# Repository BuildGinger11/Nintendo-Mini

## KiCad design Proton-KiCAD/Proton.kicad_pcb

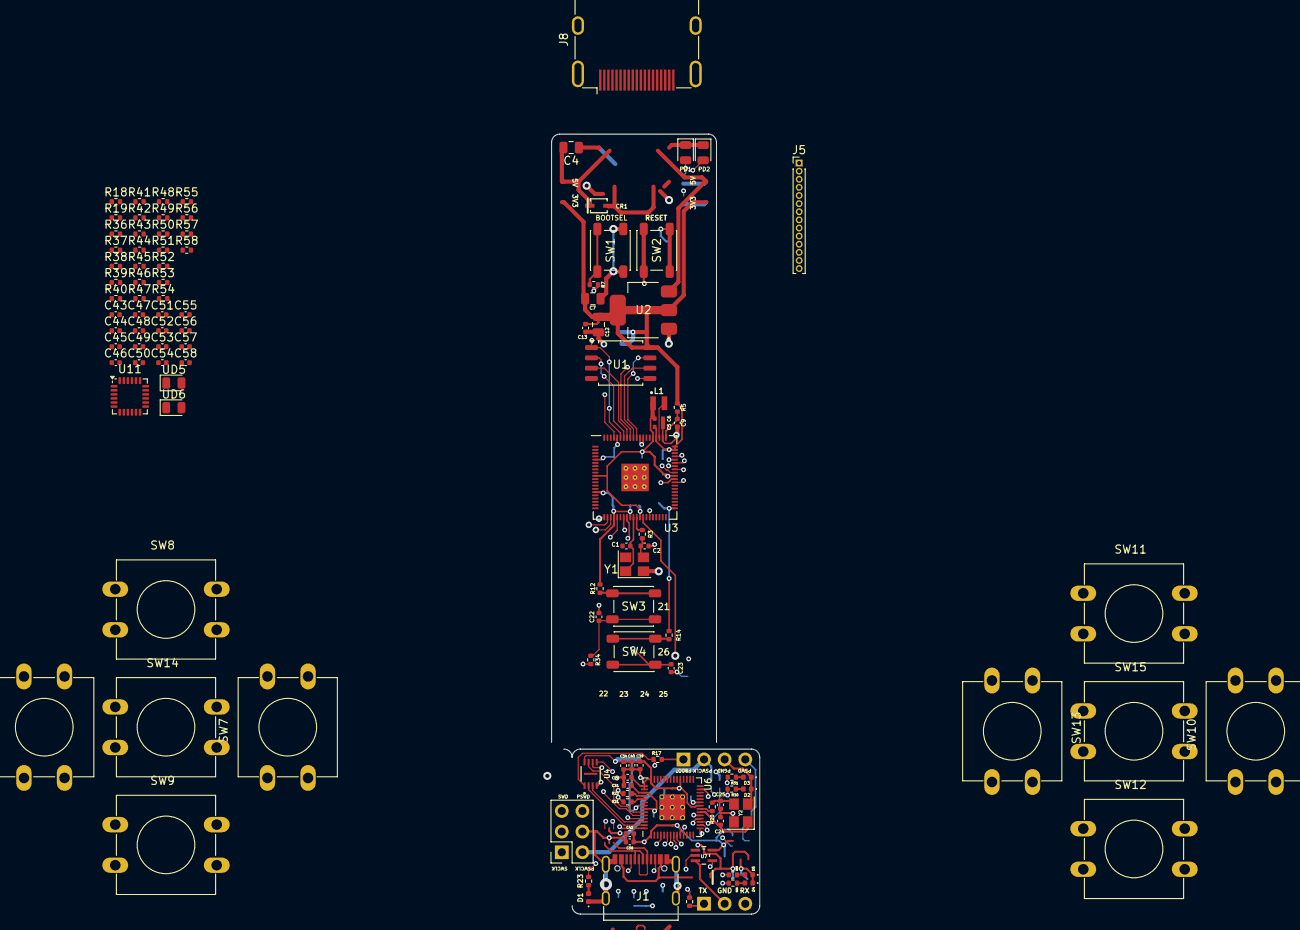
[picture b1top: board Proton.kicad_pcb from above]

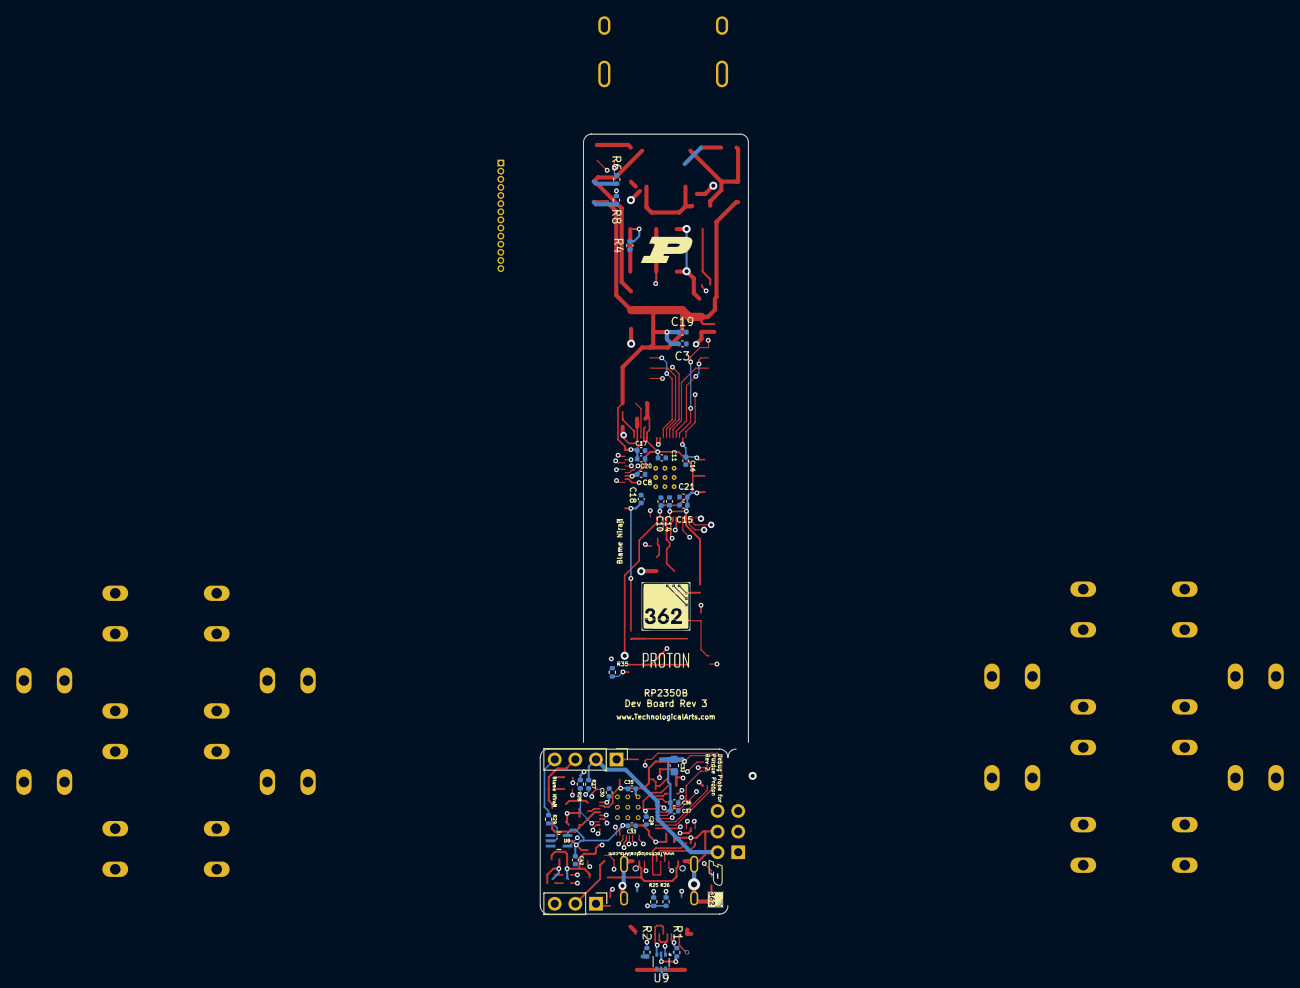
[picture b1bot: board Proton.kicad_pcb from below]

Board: 4 copper layers, 25.6 x 96.1 mm, 150 parts (35 on the bottom side), 91 nets.

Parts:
C1, C2, C24, C25: 15p; C_0402_1005Metric
C3, C8, C11, C13, C14, C15, C16, C17, C18, C19, C20, C21, C22, C23, C28, C29, C30, C33, C35, C36, C37, C38, C39, C40, C41, C42, C43, C44, C45, C46, C47, C48, C49, C50, C57, C58: 100n; C_0402_1005Metric
C4, C7, C12: 10u; C_0805_2012Metric
C5, C6: 4.7u; C_0402_1005Metric_small_pads
C9, C10, C56: 4.7u; C_0402_1005Metric
C31, C34: 1u; C_0402_1005Metric
C32: 10u; C_0603_1608Metric
C51, C53, C54, C55: 0.1u; C_0402_1005Metric
C52: 2.2n; C_0402_1005Metric
CR1: BAT60JFILM; CR_60JFILM_STM
D1: RED; D_0402_1005Metric
D2, D4: GREEN; D_0402_1005Metric
D3, D5: YELLOW; D_0402_1005Metric
J1: USB_C_Receptacle_USB2.0_14P; USB_C_Receptacle_G-Switch_GT-USB-7010ASV
J3: DebugnBoot; PinHeader_1x04_P2.54mm_Vertical
J5: Conn_01x14_Pin; PinHeader_1x14_P1.00mm_Vertical
J6: Conn_02x03_Top_Bottom; PinSocket_2x03_P2.54mm_Vertical
J7: UART-PINS; PinHeader_1x03_P2.54mm_Vertical
J8: HDMI_A; HDMI_A_Molex_208658-1001_Horizontal
L1: 3.3u; L_pol_2016
PD1: RED; LED_0805_2012Metric
PD2: GREEN; LED_0805_2012Metric
R1, R2, R6: 5.1k; R_0402_1005Metric
R3, R4, R7, R8, R12, R14, R17, R18, R19, R20, R36, R38, R40, R42, R44, R45, R46, R47, R55, R57: 1k; R_0402_1005Metric
R5: 33; R_0402_1005Metric
R21, R22: 27; R_0402_1005Metric
R23, R31, R33: 470; R_0402_1005Metric
R24, R25, R26, R27, R28, R29: 100; R_0402_1005Metric
R30, R32: 2k; R_0402_1005Metric
R34, R35, R37, R39, R41, R43, R48, R49, R50, R51, R56, R58: 10k; R_0402_1005Metric
R52: 30k; R_0402_1005Metric
R53, R54: 1.13k; R_0402_1005Metric
SW1: BOOTSEL; SW_SPST_PTS647_Sx38
SW2: RESET; SW_SPST_PTS647_Sx38
SW3: LEFT; SW_SPST_PTS647_Sx38
SW4: RIGHT; SW_SPST_PTS647_Sx38
SW6: LEFT_LEFT; SW_PUSH-12mm
SW7: LEFT_RIGHT; SW_PUSH-12mm
SW8: LEFT_UP; SW_PUSH-12mm
SW9: LEFT_DOWN; SW_PUSH-12mm
SW10: RIGHT_RIGHT; SW_PUSH-12mm
SW11: RIGHT_UP; SW_PUSH-12mm
SW12: RIGHT_DOWN; SW_PUSH-12mm
SW13: RIGHT_LEFT; SW_PUSH-12mm
SW14: LEFT_SEL; SW_PUSH-12mm
SW15: RIGHT_SEL; SW_PUSH-12mm
U1: W25Q128JVS; SOIC-8_5.23x5.23mm_P1.27mm
U2: NCP1117-3.3_SOT223; SOT-223-3_TabPin2
U3: RP2350_80QFN; RP2350-QFN-80-1EP_10x10_P0.4mm_EP3.4x3.4mm_ThermalVias
U4: W25Q16JVUXIQ TR; USON-8_UX_2x3x0p6_WIN
U6: RP2040; RP2040-QFN-56
U7, U8: SN74AUP1T17DCKR; DCK5
U9: USBLC6-2P6; SOT-666
U11: MPU-6050; InvenSense_QFN-24_4x4mm_P0.5mm
UD5, UD6: BLUE; LED_0805_2012Metric
Y1, Y2: ABM8-272-T3; Crystal_SMD_3225-4Pin_3.2x2.5mm

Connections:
+1V1: C6.1, C8.1, C10.1, C11.1, L1.1, U3.10 (DVDD), U3.32 (DVDD), U3.51 (DVDD), U3.65 (VREG_FB)
+3V3: C3.1, C5.1, C7.1, C12.1, C13.1, C14.1, C15.1, C16.1, C17.1, C18.1, C19.1, C20.1, C21.1, C29.1, C32.1, C33.1, C34.1, C35.1, C36.1, C37.1, C38.1, C39.1, C40.1, C41.1, C42.1, C53.1, C56.1, J5.1, R5.1, R8.1, R12.1, R14.1, R18.1, R19.1, R36.1, R38.1, R40.1, R42.1, R44.1, R45.1, R46.1, R47.1, R52.1, R55.1, R57.1, U1.8 (VCC), U2.2 (VO), U3.5 (IOVDD), U3.15 (IOVDD), U3.24 (IOVDD), U3.29 (IOVDD), U3.41 (IOVDD), U3.50 (IOVDD), U3.59 (ADC_AVDD), U3.60 (IOVDD), U3.64 (VREG_VIN), U3.68 (USB_OTP_VDD), U3.69 (QSPI_IOVDD), U3.76 (IOVDD), U4.8 (VCC), U6.1 (IOVDD), U6.10 (IOVDD), U6.22 (IOVDD), U6.33 (IOVDD), U6.42 (IOVDD), U6.43 (ADC_AVDD), U6.44 (VREG_IN), U6.48 (USB_VDD), U6.49 (IOVDD), U7.5 (VCC), U8.5 (VCC), U11.13 (VDD)
+P1V1: C28.1, C30.1, C31.1, U6.23 (DVDD), U6.45 (VREG_VOUT), U6.50 (DVDD)
/DebugProbe/GPIO2: R23.1, U6.4 (GPIO2)
/DebugProbe/GPIO4: R24.1, U6.6 (GPIO4)
/DebugProbe/GPIO5: U6.7 (GPIO5), U7.4 (Y)
/DebugProbe/GPIO6: R25.1, U6.8 (GPIO6)
/DebugProbe/GPIO7: R30.1, U6.9 (GPIO7)
/DebugProbe/GPIO8: R31.1, U6.11 (GPIO8)
/DebugProbe/GPIO12: R27.1, U6.15 (GPIO12)
/DebugProbe/GPIO13: U6.16 (GPIO13), U8.4 (Y)
/DebugProbe/GPIO14: R28.1, U6.17 (GPIO14)
/DebugProbe/GPIO15: R32.1, U6.18 (GPIO15)
/DebugProbe/GPIO16: R33.1, U6.27 (GPIO16)
/DebugProbe/QSPI_SCLK: U4.6 (CLK), U6.52 (QSPI_SCLK)
/DebugProbe/QSPI_SD0: U4.5 (DI(IO0)), U6.53 (QSPI_SD0)
/DebugProbe/QSPI_SD1: U4.2 (DO(IO1)), U6.55 (QSPI_SD1)
/DebugProbe/QSPI_SD2: U4.3 (/WP(IO2)), U6.54 (QSPI_SD2)
/DebugProbe/QSPI_SD3: U4.7 (/HOLDOR/RESET(IO3)), U6.51 (QSPI_SD3)
/DebugProbe/QSPI_SS: R17.1, U4.1 (/CS), U6.56 (QSPI_SS)
/DebugProbe/XIN: C24.1, U6.20 (XIN), Y2.1
/DebugProbe/XOUT: R20.1, U6.21 (XOUT)
/DebugProbe/~USB_BOOT: J3.1, R17.2
/FLASH_SS: R7.1, U1.1 (~CS), U3.75 (QSPI_SS)
/GPIO21: C22.1, R34.2, SW3.2, U3.21 (GPIO21)
/GPIO26: C23.1, R35.2, SW4.2, U3.27 (GPIO26)
/Peripherals/LEFT_DOWN: C46.1, R43.2, SW9.2
/Peripherals/LEFT_LEFT: C43.1, R37.2, SW6.2
/Peripherals/LEFT_RIGHT: C44.1, R39.2, SW7.2
/Peripherals/LEFT_SEL: C57.1, R56.2, SW14.2
/Peripherals/LEFT_UP: C45.1, R41.2, SW8.2
/Peripherals/RIGHT_DOWN: C49.1, R50.2, SW12.2
/Peripherals/RIGHT_LEFT: C50.1, R51.2, SW13.2
/Peripherals/RIGHT_RIGHT: C47.1, R48.2, SW10.2
/Peripherals/RIGHT_SEL: C58.1, R58.2, SW15.2
/Peripherals/RIGHT_UP: C48.1, R49.2, SW11.2
/QSPI_SCLK: U1.6 (CLK), U3.71 (QSPI_SCLK)
/QSPI_SD0: U1.5 (DI(IO0)), U3.72 (QSPI_SD0)
/QSPI_SD1: U1.2 (DO(IO1)), U3.74 (QSPI_SD1)
/QSPI_SD2: U1.3 (IO2), U3.73 (QSPI_SD2)
/QSPI_SD3: U1.7 (IO3), U3.70 (QSPI_SD3)
/RUN: SW2.2, U3.35 (RUN)
/SWCLK: J6.1, U3.33 (SWCLK)
/SWD: J6.5, U3.34 (SWD)
/VREG_AVDD: C9.1, R5.2, U3.61 (VREG_AVDD)
/VREG_LX: L1.2, U3.63 (VREG_LX)
/XIN: C1.1, U3.30 (XIN), Y1.1
/XOUT: R3.1, U3.31 (XOUT)
/~USB_BOOT: R7.2, SW1.2
unnamed: C2.1, R3.2, Y1.3
unnamed: C25.1, R20.2, Y2.3
unnamed: D1.2 (A), R23.2
unnamed: D2.2 (A), R30.2
unnamed: D3.2 (A), R31.2
unnamed: D4.2 (A), R32.2
unnamed: D5.2 (A), R33.2
unnamed: J1.A5 (CC1), R1.1
unnamed: J1.B5 (CC2), R2.1
unnamed: J1.A6 (D+), J1.B6 (D+), U9.3 (I/O2)
unnamed: J1.A7 (D-), J1.B7 (D-), U9.1 (I/O1)
unnamed: J7.1, R24.2
unnamed: J7.3, R25.2, R26.2
unnamed: PD1.2 (A), R6.2
unnamed: PD2.2 (A), R8.2
unnamed: R4.1, SW2.1
unnamed: R12.2, SW3.1
unnamed: R14.2, SW4.1
unnamed: R36.2, SW6.1
unnamed: R38.2, SW7.1
unnamed: R40.2, SW8.1
unnamed: R42.2, SW9.1
unnamed: R44.2, SW10.1
unnamed: R45.2, SW11.1
unnamed: R46.2, SW12.1
unnamed: R47.2, SW13.1
unnamed: R55.2, SW14.1
unnamed: R57.2, SW15.1
unnamed: R22.2, U6.46 (USB_DM)
unnamed: R21.2, U6.47 (USB_DP)
unnamed: R26.1, U7.2 (A)
unnamed: R29.1, U8.2 (A)
unnamed: C52.1, U11.20 (CPOUT)
unnamed: C51.1, U11.10 (REGOUT)
unnamed: C54.1, R52.2, U11.8 (VLOGIC)
unnamed: R18.2, UD5.2 (A)
unnamed: R19.2, UD6.2 (A)
PGND: C1.2, C2.2, C3.2, C4.2, C5.2, C6.2, C7.2, C8.2, C9.2, C10.2, C11.2, C12.2, C13.2, C14.2, C15.2, C16.2, C17.2, C18.2, C19.2, C20.2, C21.2, C22.2, C23.2, C24.2, C25.2, C28.2, C29.2, C30.2, C31.2, C32.2, C33.2, C34.2, C35.2, C36.2, C37.2, C38.2, C39.2, C40.2, C41.2, C42.2, C43.2, C44.2, C45.2, C46.2, C47.2, C48.2, C49.2, C50.2, C51.2, C52.2, C53.2, C54.2, C55.2, C56.2, C57.2, C58.2, D1.1 (K), D2.1 (K), D3.1 (K), D4.1 (K), D5.1 (K), J1.A1 (GND), J1.A12 (GND), J1.B1 (GND), J1.B12 (GND), J1.S1 (SHIELD), J3.3, J5.2, J6.3, J6.4, J7.2, PD1.1 (K), PD2.1 (K), R1.2, R2.2, R4.2, R34.1, R35.1, R37.1, R39.1, R41.1, R43.1, R48.1, R49.1, R50.1, R51.1, R53.2, R54.2, R56.1, R58.1, SW1.1, U1.4 (GND), U2.1 (GND), U3.62 (VREG_PGND), U3.81 (GND), U4.4 (GND), U6.19 (TESTEN), U6.57 (GND), U7.3 (GND), U8.3 (GND), U9.2 (GND), U11.18 (GND), Y1.2, Y1.4, Y2.2, Y2.4
PSWCLK: J3.2, J6.2, R27.2
PSWD: J3.4, J6.6, R28.2, R29.2
UVBUS: C55.1, CR1.2, J1.A4 (VBUS), J1.A9 (VBUS), J1.B4 (VBUS), J1.B9 (VBUS), U9.5 (VBUS)
VBUS: C4.1, CR1.1, J8.18 (+5V_18), R6.1, U2.3 (VI)

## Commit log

2026-03-29 Added Proton Board
2026-03-31 Added Buttons and IMU
2026-03-31 Fixed to higherarchical labels
2026-04-01 Added Battery Charger
2026-04-03 Added Pinouts
2026-04-03 Started layout
2026-04-03 continued layout
